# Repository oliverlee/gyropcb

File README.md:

This set of PCBs are designed to use with various projects in the
[phobos](https://github.com/oliverlee/phobos) repository. The PCBs are designed
to be used with the following items:
- [OLIMEX STM32-H405](https://www.olimex.com/Products/ARM/ST/STM32-H405/)
- [Maxon ESCON Module 50//5](http://www.maxonmotor.com/maxon/view/product/control/4-Q-Servokontroller/438725)

## Bill of Materials
The bill of materials is maintained [here](https://docs.google.com/spreadsheets/d/1CJe4dBAEXy64Y3e8YSP1X_Nll6x3aowWz7-QJbUk4VQ/edit?usp=sharing)

It may be out of date so take a look at it carefully.

## Notes
- In order to use the SDIO peripheral, R27 on the OLIMEX STM32-H405 must be
  disconnected from from the SDIO_CMD line (EXT1-11). This can be done by
  cutting the trace connecting EXT1-11 and R27.

## Errata
### v0.1
### mc pcb
- Description for solder jumper switch S3 on silkscreen layer is reversed.
- Description for solder jumper switch S4 on silkscreen layer is reversed.
- SDIO CMD line missing pullup resistor. A 33k resistor can be added at EXT1
  connecting pins 5 and 11. The leads must be kept as short as possible to
  minimize overshoot and ringing.

### power pcb
- +24V mount pad not connected to +24V rail.
- GND mount pad not connected to ground planes.
- The measure line of the Kistler torque sensor cannot be pulled to ground. A
  fix requires the removal of transistor Q2 and the measure line to be connected
  to the collector end of transistor Q1. This bypasses and disables switch S1.
- Description for solder jumper switch S2 on silkscreen layer is reversed.
- Silkscreen on J1, J3 incorrect: WIND1 and WIND2 reversed.
- Trace for HALL2_S2 between Ext3 and J3 is completely missing.
- J1, J3 molex pins can not withstand motor windings 1,2,3 current. Motor windings cable must be connected directly to motor dive. Check drawing for new molex types used to rearrange the new connection.
- J1, J2 male molex vertical headers must be changed with right hand angle headers to allow motor drive fit to Ext2 & Ext1. Check drawing file for new headers used to make the rearrangement.

For the steer by wire bicycle project the following changes were made:
### power pcb
18 Voltage regulator switched from LM2576S TO LM2576HV to withstand higher voltage since power supply voltage was switched from 24v to 36v.
### mc_pcb
Multiplexers 74AC157D were removed since Giel mentioned that there was an issue with the supply voltage. 
The inputs and outputs pins of the multiplexers were connected with cables. U4 now gives an output of ENC1_CHA+CHB and ENC2_CHA+CHB. 
Rear wheel encoder must be connected directly to microcontroller. U5 gives the output of PEDAL_ENC_A +ENC_B.

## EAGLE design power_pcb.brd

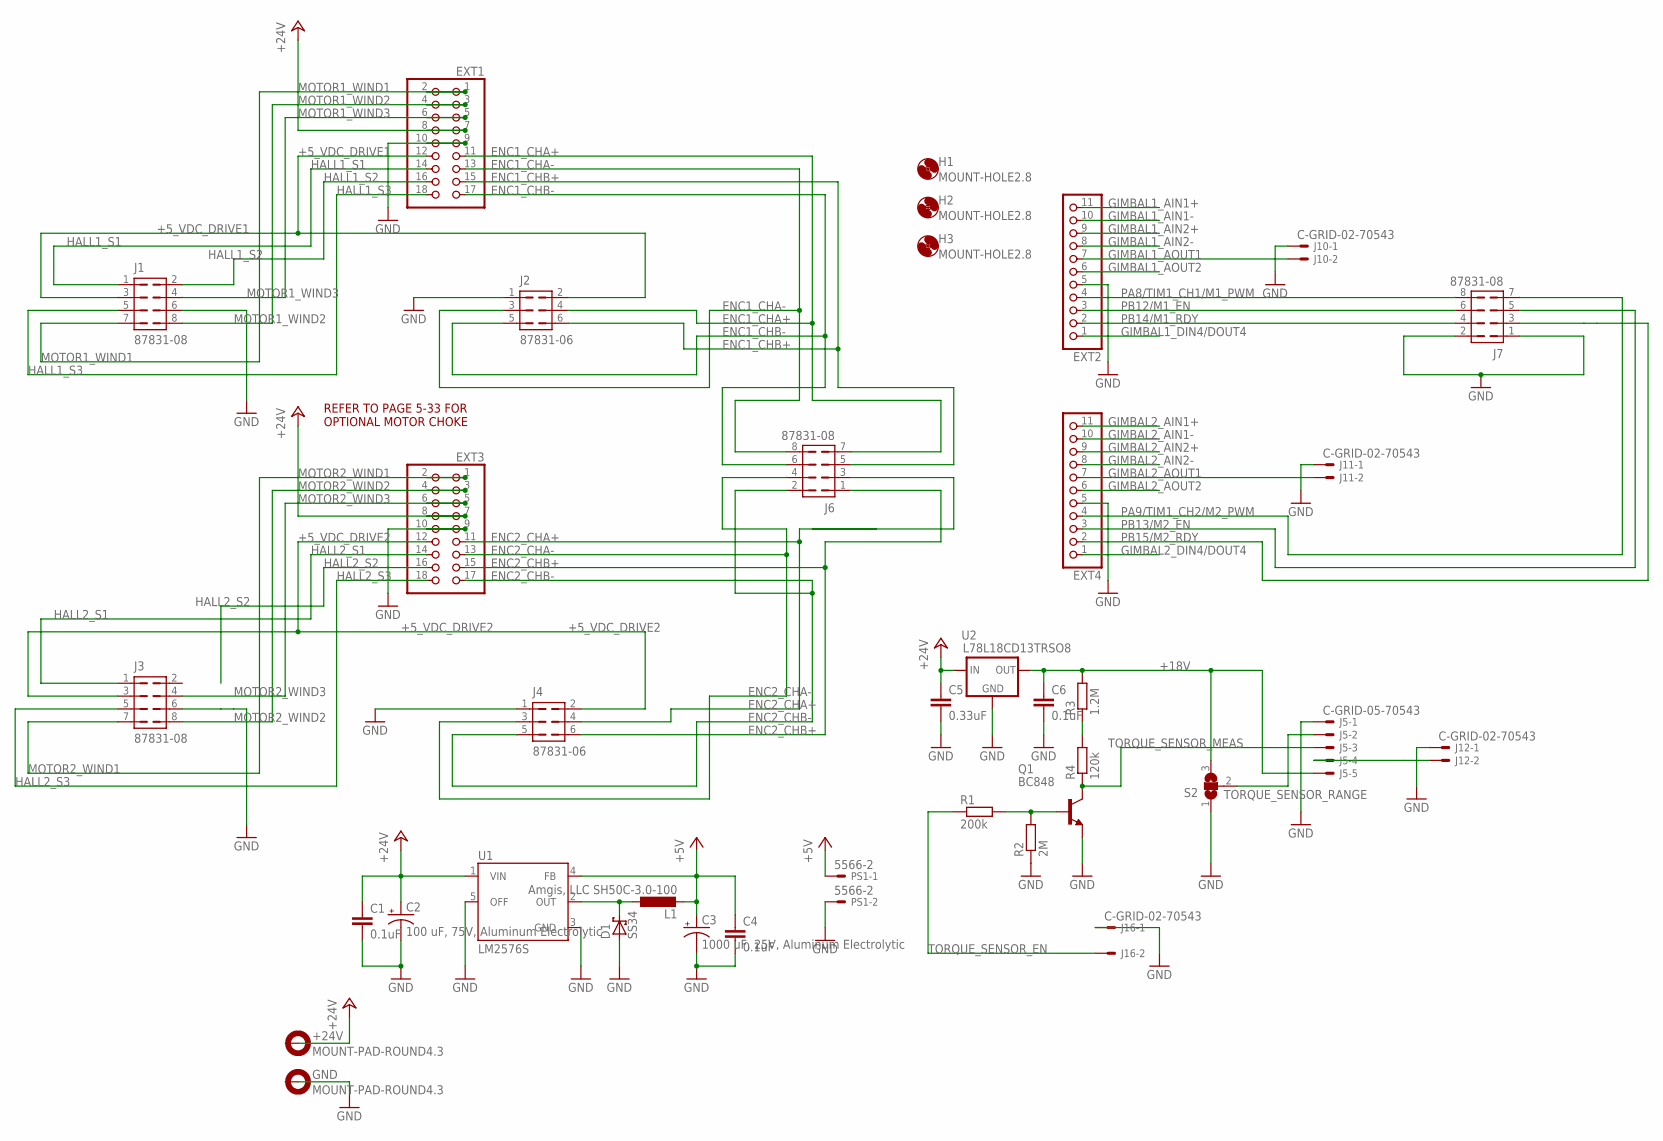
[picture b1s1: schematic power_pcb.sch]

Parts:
+24V: MOUNT-PAD-ROUND4.3; 4,3-PAD
C1, C4, C6: 0.1uF; C0603
C2: 100 uF, 75V, Aluminum Electrolytic; PANASONIC_H13
C3: 1000 uF, 25V, Aluminum Electrolytic; PANASONIC_H13
C5: 0.33uF; C0603
D1: SS34; SMC
EXT1, EXT3: PINHD-2X9; 2X09
EXT2, EXT4: PINHD-1X11; 1X11
GND: MOUNT-PAD-ROUND4.3; 4,3-PAD
H1, H2, H3: MOUNT-HOLE2.8; 2,8
J1, J3, J6, J7: 87831-08
J2, J4: 87831-06
J5: C-GRID-05-70543; 70543-05
J10, J11, J12, J16: C-GRID-02-70543; 70543-02
L1: Amgis, LLC SH50C-3.0-100; SH50C-C4
PS1: 5566-2
Q1: BC848; SOT23
R1: 200k; R0603
R2: 2M; R0603
R3: 1.2M; R1210
R4: 120k; R1210
S2: SJ2W; SJ_2
U1: LM2576S; TO263-5
U2: L78L18CD13TRSO8; SO8-VREG

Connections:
+5V: C3.+, C4.1, L1.P$2 (2), PS1.1, U1.4 (FB)
+5_VDC_DRIVE1: EXT1.12, J1.3, J2.2
+5_VDC_DRIVE2: EXT3.12, J3.3, J4.2
+18V: C6.1, J5.5, R3.2, S2.3, U2.1 (OUT)
+24V: C1.1, C2.+, C5.1, EXT1.7, EXT1.8, EXT3.7, EXT3.8, U1.1 (VIN), U2.8 (IN)
ENC1_CHA+: EXT1.11, J2.4, J6.7
ENC1_CHA-: EXT1.13, J2.3, J6.8
ENC1_CHB+: EXT1.15, J2.6, J6.5
ENC1_CHB-: EXT1.17, J2.5, J6.6
ENC2_CHA+: EXT3.11, J4.4, J6.3
ENC2_CHA-: EXT3.13, J4.3, J6.4
ENC2_CHB+: EXT3.15, J4.6, J6.1
ENC2_CHB-: EXT3.17, J4.5, J6.2
GIMBAL1_AIN1+: EXT2.11
GIMBAL1_AIN1-: EXT2.10
GIMBAL1_AIN2+: EXT2.9
GIMBAL1_AIN2-: EXT2.8
GIMBAL1_AOUT1: EXT2.7, J10.2
GIMBAL1_AOUT2: EXT2.6
GIMBAL1_DIN4/DOUT4: EXT2.1
GIMBAL2_AIN1+: EXT4.11
GIMBAL2_AIN1-: EXT4.10
GIMBAL2_AIN2+: EXT4.9
GIMBAL2_AIN2-: EXT4.8
GIMBAL2_AOUT1: EXT4.7, J11.2
GIMBAL2_AOUT2: EXT4.6
GIMBAL2_DIN4/DOUT4: EXT4.1
GND: C1.2, C2.-, C3.-, C4.2, C5.2, C6.2, D1.A, EXT1.9, EXT1.10, EXT2.5, EXT3.9, EXT3.10, EXT4.5, J1.6, J2.1, J3.6, J4.1, J5.1, J7.1, J7.2, J10.1, J11.1, J12.1, J16.1, PS1.2, Q1.2 (E), R2.1, S2.1, U1.3 (GND), U1.5 (OFF), U2.2 (GND), U2.3 (GND), U2.6 (GND), U2.7 (GND)
HALL1_S1: EXT1.14, J1.1
HALL1_S2: EXT1.16, J1.2
HALL1_S3: EXT1.18, J1.5
HALL2_S1: EXT3.14, J3.1
HALL2_S2: EXT3.16
HALL2_S3: EXT3.18, J3.5
MOTOR1_WIND1: EXT1.1, EXT1.2, J1.7
MOTOR1_WIND2: EXT1.3, EXT1.4, J1.8
MOTOR1_WIND3: EXT1.5, EXT1.6, J1.4
MOTOR2_WIND1: EXT3.1, EXT3.2, J3.7
MOTOR2_WIND2: EXT3.3, EXT3.4, J3.8
MOTOR2_WIND3: EXT3.5, EXT3.6, J3.4
unnamed: J5.4, J12.2
unnamed: D1.C, L1.P$1 (1), U1.2 (OUT)
unnamed: R3.1, R4.2
unnamed: Q1.1 (B), R1.2, R2.2
PA8/TIM1_CH1/M1_PWM: EXT2.4, J7.8
PA9/TIM1_CH2/M2_PWM: EXT4.4, J7.7
PB12/M1_EN: EXT2.3, J7.6
PB13/M2_EN: EXT4.3, J7.5
PB14/M1_RDY: EXT2.2, J7.4
PB15/M2_RDY: EXT4.2, J7.3
TORQUE_SENSOR_EN: J16.2, R1.1
TORQUE_SENSOR_MEAS: J5.3, Q1.3 (C), R4.1
TORQUE_SENSOR_RANGE: J5.2, S2.2

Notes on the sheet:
REFER TO PAGE 5-33 FOR OPTIONAL MOTOR CHOKE

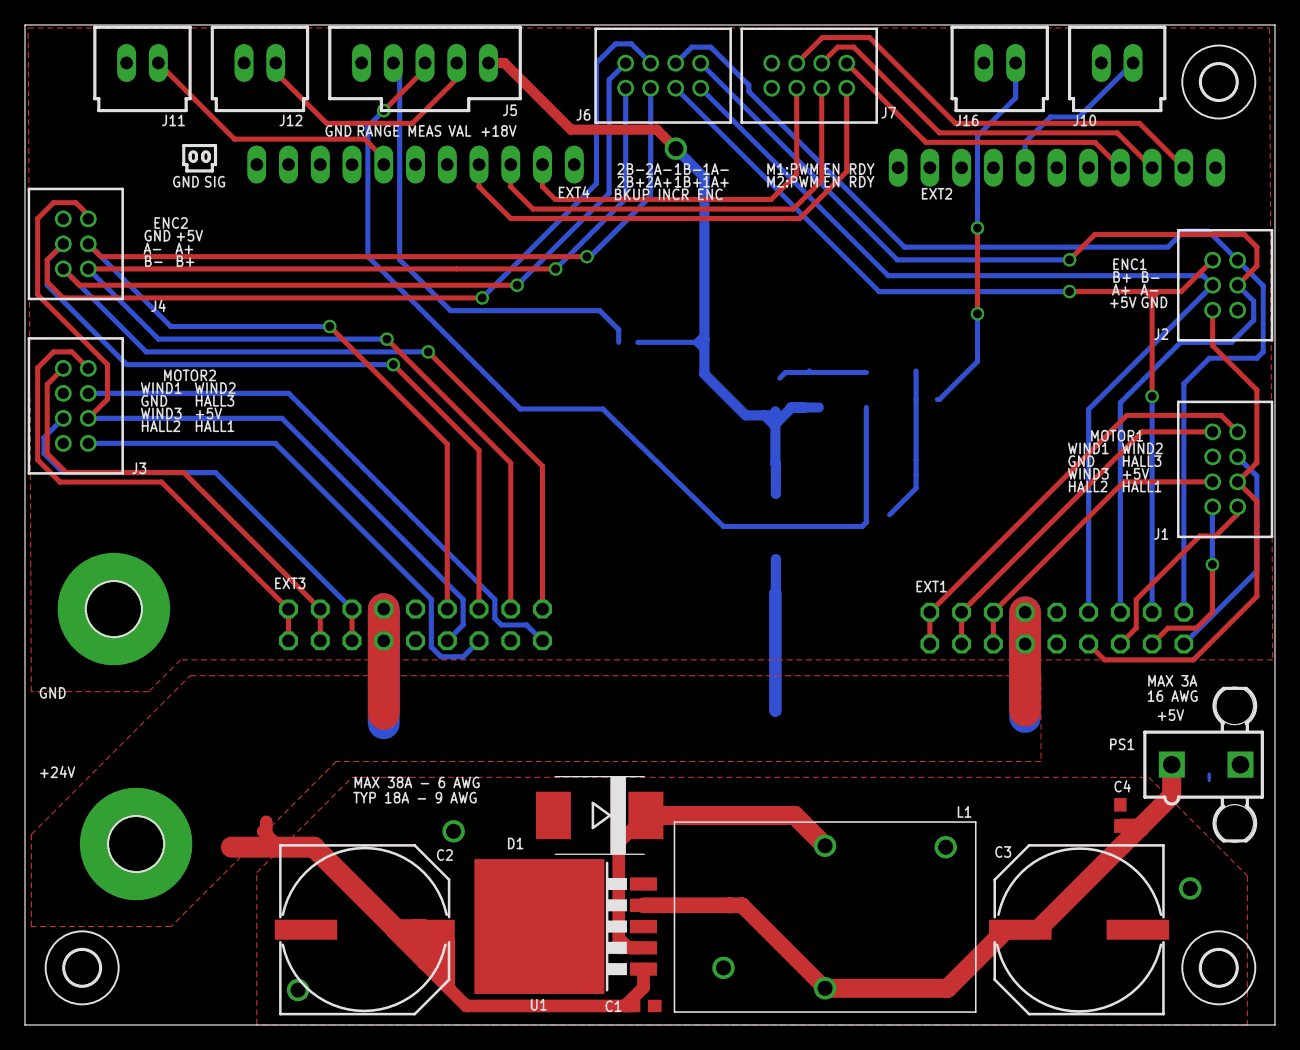
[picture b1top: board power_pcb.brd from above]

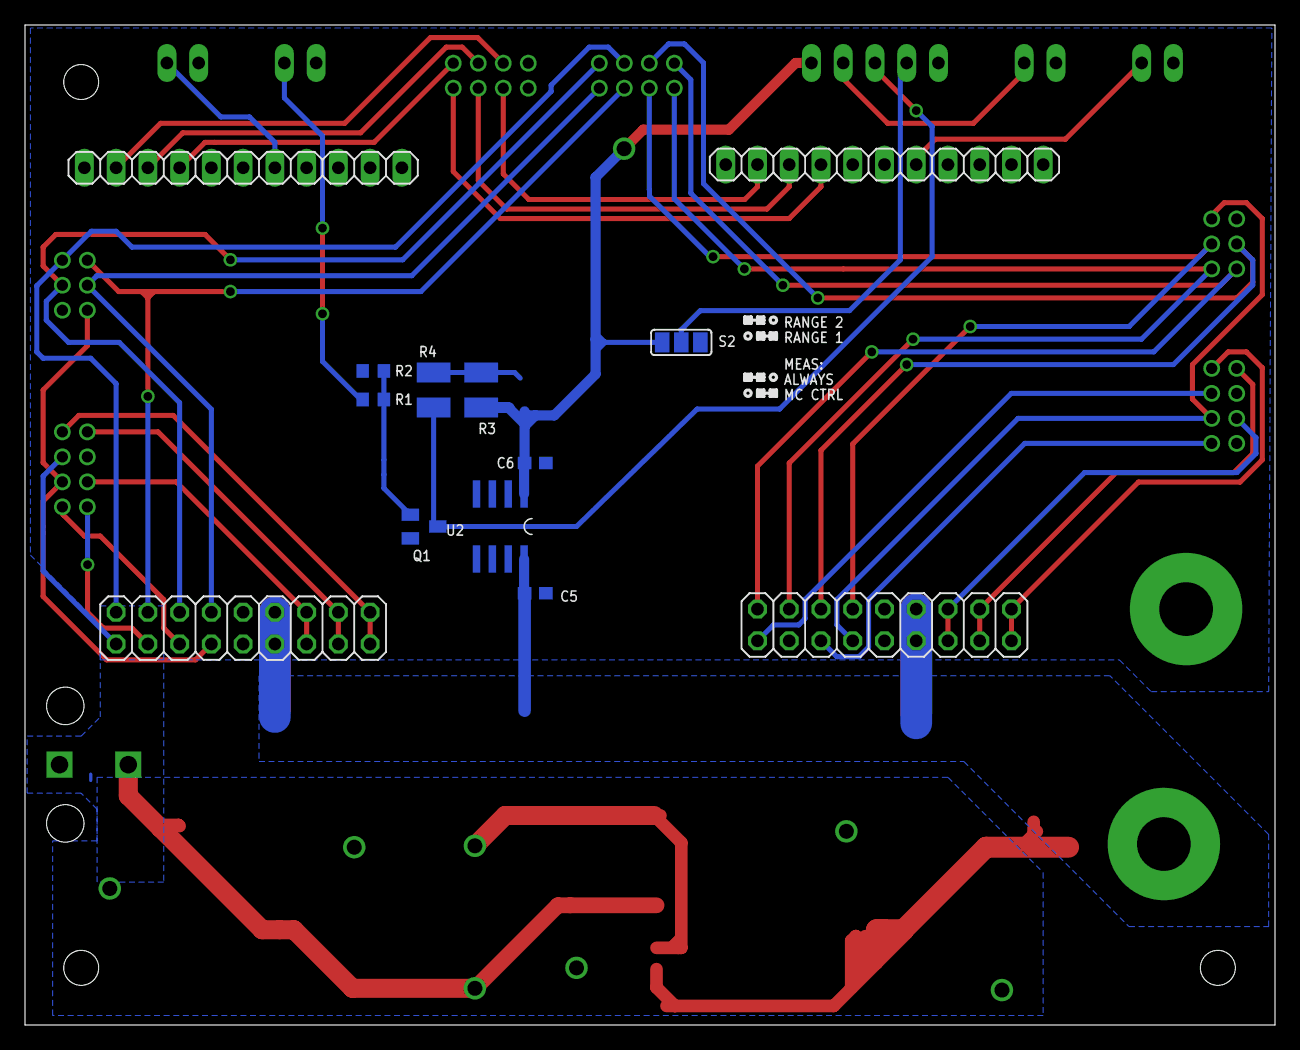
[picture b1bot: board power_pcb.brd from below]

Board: 8 copper layers, 100.0 x 80.0 mm, 37 parts (13 on the bottom side), 40 nets.

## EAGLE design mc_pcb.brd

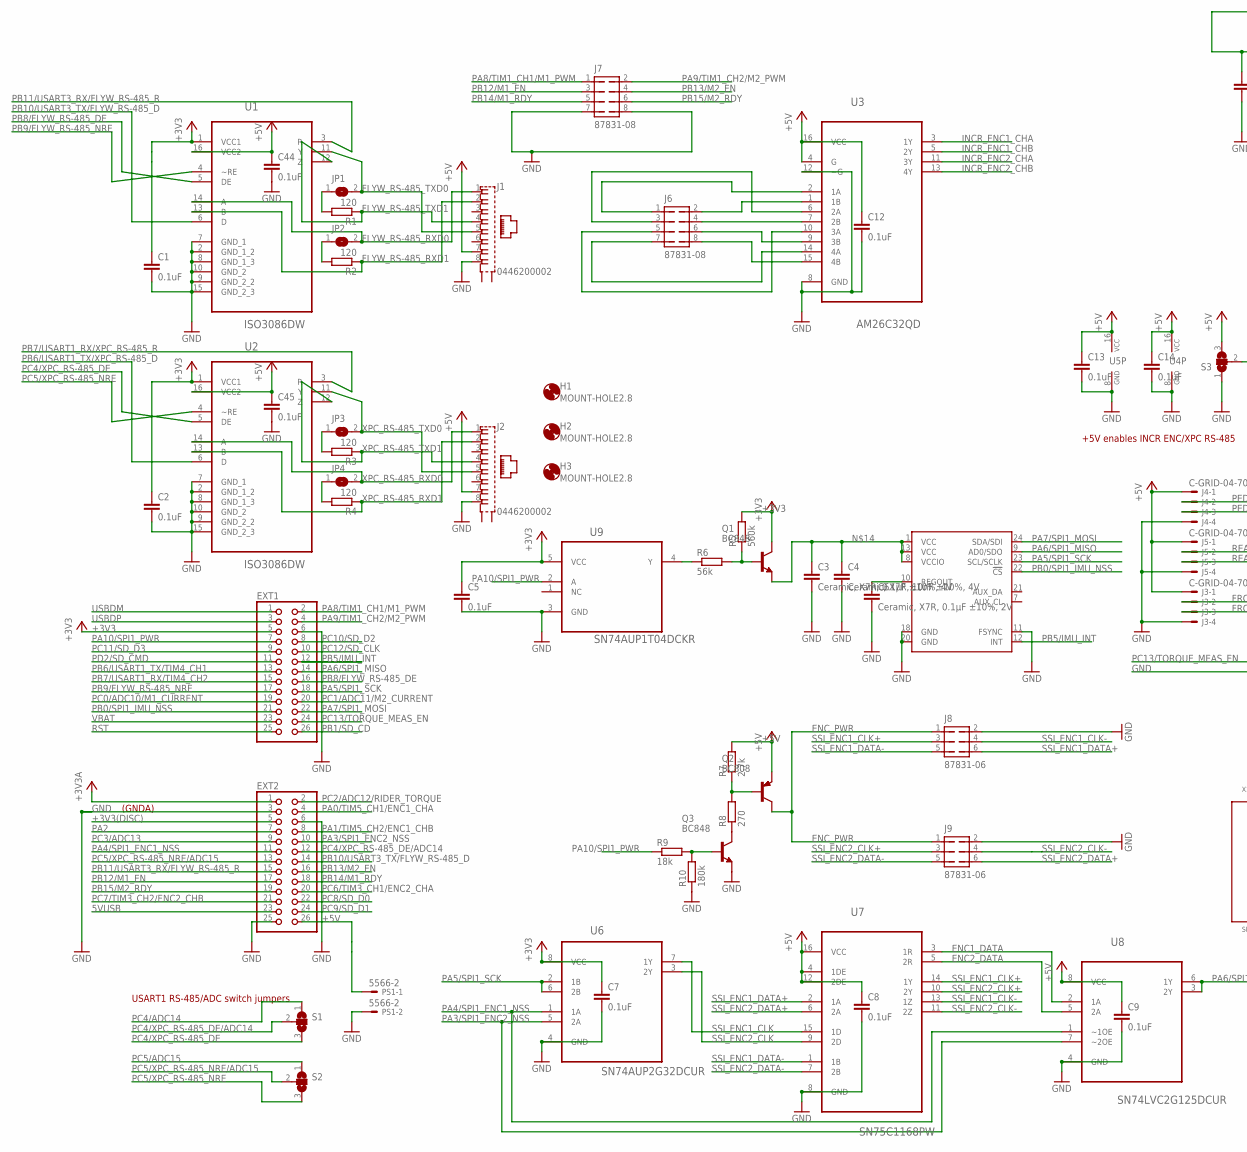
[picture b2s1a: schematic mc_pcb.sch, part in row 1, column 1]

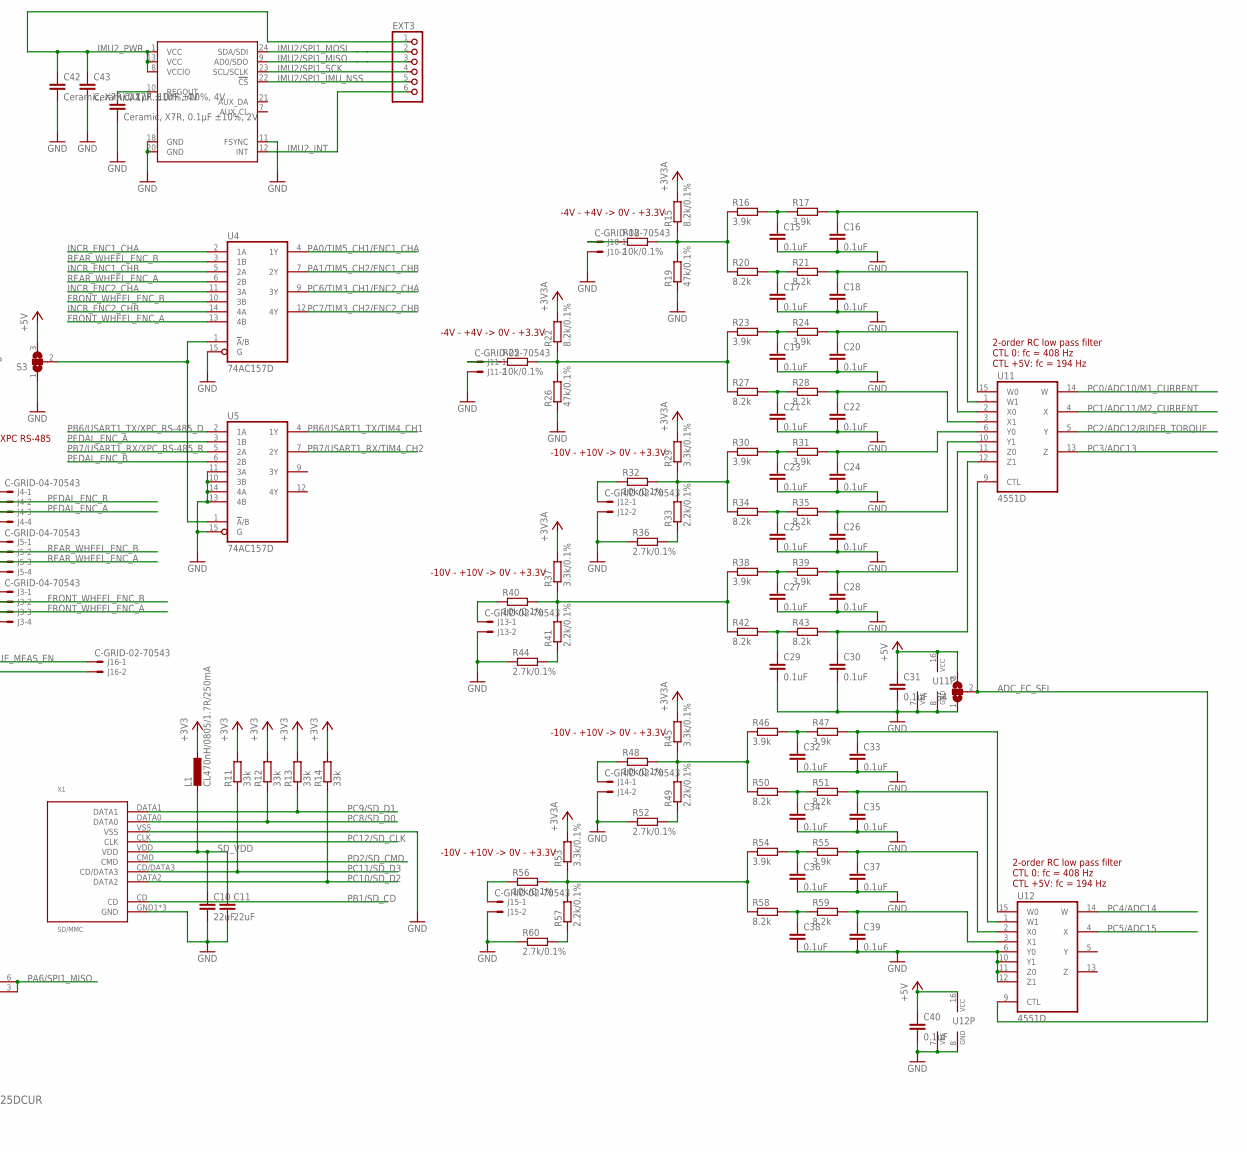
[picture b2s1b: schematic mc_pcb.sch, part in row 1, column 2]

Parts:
C1, C2, C5, C7, C8, C9, C12, C13, C14, C15, C16, C17, C18, C19, C20, C21, C22, C23, C24, C25, C26, C27, C28, C29, C30, C31, C32, C33, C34, C35, C36, C37, C38, C39, C40, C44, C45: 0.1uF; C0603
C3, C42: Ceramic, X7R, 0.1μF ±10%, 4V; C0603
C4, C43: Ceramic, X7R, 10nF ±10%, 4V; C0603
C6, C41: Ceramic, X7R, 0.1μF ±10%, 2V; C0603
C10, C11: 22uF; C0603
EXT1, EXT2: PINHD-2X13; 2X13
EXT3: PINHD-1X6; 1X06
H1, H2, H3: MOUNT-HOLE2.8; 2,8
J1, J2: 0446200002
J3, J4, J5: C-GRID-04-70543; 70543-04
J6, J7: 87831-08
J8, J9: 87831-06
J10, J11, J12, J13, J14, J15, J16: C-GRID-02-70543; 70543-02
JP1, JP2, JP3, JP4: SJ
L1: CL470nH/0805/1.7R/250mA; L2012C
PS1: 5566-2
Q1, Q3: BC848; SOT23
Q2: BC808; SOT23-BEC
R1, R2, R3, R4: 120; R0603
R5: 560k; R0603
R6: 56k; R0603
R7: 2.7k; R1210
R8: 270; R1210
R9: 18k; R0603
R10: 180k; R0603
R11, R12, R13, R14: 33k; R0603
R15, R22: 8.2k/0.1%; R0603
R16, R17, R23, R24, R30, R31, R38, R39, R46, R47, R54, R55: 3.9k; R0603
R18, R25, R32, R40, R48, R56: 10k/0.1%; R0603
R19, R26: 47k/0.1%; R0603
R20, R21, R27, R28, R34, R35, R42, R43, R50, R51, R58, R59: 8.2k; R0603
R29, R37, R45, R53: 3.3k/0.1%; R0603
R33, R41, R49, R57: 2.2k/0.1%; R0603
R36, R44, R52, R60: 2.7k/0.1%; R0603
S1, S2, S3, S4: SJ2W; SJ_2
U1, U2: ISO3086DW; SOIC127P1030X265-16N
U3: AM26C32QD; SOIC127P600X175-16N
U4, U5: 74AC157D; SO16
U6: SN74AUP2G32DCUR; SOP50P310X90-8N
U7: SN75C1168PW; SOP65P640X120-16N
U8: SN74LVC2G125DCUR; SOP50P310X90-8N
U9: SN74AUP1T04DCKR; SOT65P210X110-5N
U10, U13: MPU-9250; QFN24-SMALL
U11, U12: 4551D; SO16
X1: 10100660; -68-6

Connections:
5VUSB: EXT2.23
+3V3: C1.1, C2.1, C5.1, C7.1, EXT1.5, L1.1, Q1.3 (C), R5.2, R11.2, R12.2, R13.2, R14.2, U1.1 (VCC1), U2.1 (VCC1), U6.8 (VCC), U9.5 (VCC)
+3V3(DISC): EXT2.5
+3V3A: EXT2.1, R15.2, R22.2, R29.2, R37.2, R45.2, R53.2
+5V: C8.1, C9.1, C12.1, C13.1, C14.1, C31.1, C40.1, C44.1, C45.1, EXT2.26, J1.7, J2.7, J3.1, J4.1, J5.1, PS1.1, Q2.E, R7.2, S3.3, S4.3, U1.16 (VCC2), U2.16 (VCC2), U3.4 (G), U3.16 (VCC), U4.16 (VCC), U5.16 (VCC), U7.4 (1DE), U7.12 (2DE), U7.16 (VCC), U8.8 (VCC), U11.16 (VCC), U12.16 (VCC)
ADC_FC_SEL: S4.2, U11.9 (CTL), U12.9 (CTL)
ENC1_CHA+: J6.2, U3.1 (1B)
ENC1_CHA-: J6.1, U3.2 (1A)
ENC1_CHB+: J6.4, U3.7 (2B)
ENC1_CHB-: J6.3, U3.6 (2A)
ENC1_DATA: U7.3 (1R), U8.2 (1A)
ENC2_CHA+: J6.6, U3.9 (3B)
ENC2_CHA-: J6.5, U3.10 (3A)
ENC2_CHB+: J6.8, U3.15 (4B)
ENC2_CHB-: J6.7, U3.14 (4A)
ENC2_DATA: U7.5 (2R), U8.5 (2A)
ENC_PWR: J8.1, J9.1, Q2.C
FLYW_RS-485_RXD0: J1.1, JP2.2, U1.14 (A)
FLYW_RS-485_RXD1: J1.2, R2.1, U1.13 (B)
FLYW_RS-485_TXD0: J1.5, JP1.2, U1.11 (Y)
FLYW_RS-485_TXD1: J1.4, R1.1, U1.12 (Z)
FRONT_WHEEL_ENC_A: J3.3, U4.13 (4B)
FRONT_WHEEL_ENC_B: J3.2, U4.10 (3B)
GND: C1.2, C2.2, C3.2, C4.2, C5.2, C6.2, C7.2, C8.2, C9.2, C10.2, C11.2, C12.2, C13.2, C14.2, C15.2, C16.2, C17.2, C18.2, C19.2, C20.2, C21.2, C22.2, C23.2, C24.2, C25.2, C26.2, C27.2, C28.2, C29.2, C30.2, C31.2, C32.2, C33.2, C34.2, C35.2, C36.2, C37.2, C38.2, C39.2, C40.2, C41.2, C42.2, C43.2, C44.2, C45.2, EXT1.6, EXT2.3, EXT2.6, EXT2.25, J1.8, J2.8, J3.4, J4.4, J5.4, J7.7, J7.8, J8.2, J9.2, J10.2, J11.2, J12.2, J13.2, J14.2, J15.2, J16.2, PS1.2, Q3.2 (E), R10.1, R19.1, R26.1, R36.1, R44.1, R52.1, R60.1, S3.1, S4.1, U1.2 (GND_1_2), U1.7 (GND_1), U1.8 (GND_1_3), U1.9 (GND_2_2), U1.10 (GND_2), U1.15 (GND_2_3), U2.2 (GND_1_2), U2.7 (GND_1), U2.8 (GND_1_3), U2.9 (GND_2_2), U2.10 (GND_2), U2.15 (GND_2_3), U3.8 (GND), U3.12 (~G), U4.8 (GND), U4.15 (G), U5.8 (GND), U5.10 (3B), U5.11 (3A), U5.13 (4B), U5.14 (4A), U5.15 (G), U6.4 (GND), U7.8 (GND), U8.4 (GND), U9.3 (GND), U10.11 (FSYNC), U10.18 (GND), U10.20 (GND), U11.7 (VEE), U11.8 (GND), U12.6 (Y0), U12.7 (VEE), U12.8 (GND), U12.10 (Y1), U12.11 (Z0), U12.12 (Z1), U13.11 (FSYNC), U13.18 (GND), U13.20 (GND), X1.GND1 (GND), X1.GND2 (GND), X1.GND3 (GND), X1.VSS
IMU2/SPI1_IMU_NSS: EXT3.5, U13.22 (!CS)
IMU2/SPI1_MISO: EXT3.3, U13.9 (AD0/SDO)
IMU2/SPI1_MOSI: EXT3.2, U13.24 (SDA/SDI)
IMU2/SPI1_SCK: EXT3.4, U13.23 (SCL/SCLK)
IMU2_INT: EXT3.6, U13.12 (INT)
IMU2_PWR: C42.1, C43.1, EXT3.1, U13.1 (VCC), U13.8 (VCCIO), U13.13 (VCC)
INCR_ENC1_CHA: U3.3 (1Y), U4.2 (1A)
INCR_ENC1_CHB: U3.5 (2Y), U4.5 (2A)
INCR_ENC2_CHA: U3.11 (3Y), U4.11 (3A)
INCR_ENC2_CHB: U3.13 (4Y), U4.14 (4A)
unnamed: C6.1, U10.10 (REGOUT)
unnamed: Q1.1 (B), R5.1, R6.2
unnamed: Q2.B, R7.1, R8.2
unnamed: Q3.3 (C), R8.1
unnamed: Q3.1 (B), R9.2, R10.2
unnamed: R33.1, R36.2
unnamed: R29.1, R30.1, R32.2, R33.2, R34.1
unnamed: C41.1, U13.10 (REGOUT)
unnamed: C3.1, C4.1, Q1.2 (E), U10.1 (VCC), U10.8 (VCCIO), U10.13 (VCC)
unnamed: R15.1, R16.1, R18.2, R19.2, R20.1
unnamed: R37.1, R38.1, R40.2, R41.2, R42.1
unnamed: JP1.1, R1.2
unnamed: JP3.1, R3.2
unnamed: C32.1, R46.2, R47.1
unnamed: C33.1, R47.2, U12.15 (W0)
unnamed: C34.1, R50.2, R51.1
unnamed: C35.1, R51.2, U12.1 (W1)
unnamed: C36.1, R54.2, R55.1
unnamed: C37.1, R55.2, U12.2 (X0)
unnamed: C38.1, R58.2, R59.1
unnamed: C39.1, R59.2, U12.3 (X1)
unnamed: R6.1, U9.4 (Y)
unnamed: J15.1, R56.1
unnamed: R22.1, R23.1, R25.2, R26.2, R27.1
unnamed: J14.1, R48.1
unnamed: S3.2, U4.1 (!A!/B), U5.1 (!A!/B)
unnamed: J12.1, R32.1
unnamed: JP2.1, R2.2
unnamed: JP4.1, R4.2
unnamed: J10.1, R18.1
unnamed: C23.1, R30.2, R31.1
unnamed: C24.1, R31.2, U11.6 (Y0)
unnamed: R41.1, R44.2
unnamed: R45.1, R46.1, R48.2, R49.2, R50.1
unnamed: R49.1, R52.2
unnamed: R53.1, R54.1, R56.2, R57.2, R58.1
unnamed: R57.1, R60.2
unnamed: J13.1, R40.1
unnamed: C25.1, R34.2, R35.1
unnamed: C26.1, R35.2, U11.10 (Y1)
unnamed: C27.1, R38.2, R39.1
unnamed: C28.1, R39.2, U11.11 (Z0)
unnamed: C29.1, R42.2, R43.1
unnamed: C30.1, R43.2, U11.12 (Z1)
unnamed: C15.1, R16.2, R17.1
unnamed: C16.1, R17.2, U11.15 (W0)
unnamed: C17.1, R20.2, R21.1
unnamed: C18.1, R21.2, U11.1 (W1)
unnamed: C19.1, R23.2, R24.1
unnamed: C20.1, R24.2, U11.2 (X0)
unnamed: C21.1, R27.2, R28.1
unnamed: C22.1, R28.2, U11.3 (X1)
PA0/TIM5_CH1/ENC1_CHA: EXT2.4, U4.4 (1Y)
PA1/TIM5_CH2/ENC1_CHB: EXT2.8, U4.7 (2Y)
PA2: EXT2.7
PA3/SPI1_ENC2_NSS: EXT2.10, U6.5 (2A), U8.7 (~2OE)
PA4/SPI1_ENC1_NSS: EXT2.11, U6.1 (1A), U8.1 (~1OE)
PA5/SPI1_SCK: EXT1.18, U6.2 (1B), U6.6 (2B), U10.23 (SCL/SCLK)
PA6/SPI1_MISO: EXT1.14, U8.3 (2Y), U8.6 (1Y), U10.9 (AD0/SDO)
PA7/SPI1_MOSI: EXT1.22, U10.24 (SDA/SDI)
PA8/TIM1_CH1/M1_PWM: EXT1.2, J7.1
PA9/TIM1_CH2/M2_PWM: EXT1.4, J7.2
PA10/SPI1_PWR: EXT1.7, R9.1, U9.2 (A)
PB0/SPI1_IMU_NSS: EXT1.21, U10.22 (!CS)
PB1/SD_CD: EXT1.26, X1.CD
PB5/IMU_INT: EXT1.12, U10.12 (INT)
PB6/USART1_TX/TIM4_CH1: EXT1.13, U5.4 (1Y)
PB6/USART1_TX/XPC_RS-485_D: U2.6 (D), U5.2 (1A)
PB7/USART1_RX/TIM4_CH2: EXT1.15, U5.7 (2Y)
PB7/USART1_RX/XPC_RS-485_R: U2.3 (R), U5.5 (2A)
PB8/FLYW_RS-485_DE: EXT1.16, U1.5 (DE)
PB9/FLYW_RS-485_NRE: EXT1.17, U1.4 (~RE)
PB10/USART3_TX/FLYW_RS-485_D: EXT2.14, U1.6 (D)
PB11/USART3_RX/FLYW_RS-485_R: EXT2.15, U1.3 (R)
PB12/M1_EN: EXT2.17, J7.3
PB13/M2_EN: EXT2.16, J7.4
PB14/M1_RDY: EXT2.18, J7.5
PB15/M2_RDY: EXT2.19, J7.6
PC0/ADC10/M1_CURRENT: EXT1.19, U11.14 (W)
PC1/ADC11/M2_CURRENT: EXT1.20, U11.4 (X)
PC2/ADC12/RIDER_TORQUE: EXT2.2, U11.5 (Y)
PC3/ADC13: EXT2.9, U11.13 (Z)
PC4/ADC14: S1.1, U12.14 (W)
PC4/XPC_RS-485_DE: S1.3, U2.5 (DE)
PC4/XPC_RS-485_DE/ADC14: EXT2.12, S1.2
PC5/ADC15: S2.1, U12.4 (X)
PC5/XPC_RS-485_NRE: S2.3, U2.4 (~RE)
PC5/XPC_RS-485_NRE/ADC15: EXT2.13, S2.2
PC6/TIM3_CH1/ENC2_CHA: EXT2.20, U4.9 (3Y)
PC7/TIM3_CH2/ENC2_CHB: EXT2.21, U4.12 (4Y)
PC8/SD_D0: EXT2.22, R12.1, X1.DATA0
PC9/SD_D1: EXT2.24, R13.1, X1.DATA1
PC10/SD_D2: EXT1.8, R14.1, X1.DATA2
PC11/SD_D3: EXT1.9, R11.1, X1.CD/DATA3
PC12/SD_CLK: EXT1.10, X1.CLK
PC13/TORQUE_MEAS_EN: EXT1.24, J16.1
PD2/SD_CMD: EXT1.11, X1.CMD
PEDAL_ENC_A: J4.3, U5.3 (1B)
PEDAL_ENC_B: J4.2, U5.6 (2B)
REAR_WHEEL_ENC_A: J5.3, U4.6 (2B)
REAR_WHEEL_ENC_B: J5.2, U4.3 (1B)
RST: EXT1.25
SD_VDD: C10.1, C11.1, L1.2, X1.VDD
SSI_ENC1_CLK: U6.7 (1Y), U7.15 (1D)
SSI_ENC1_CLK+: J8.3, U7.14 (1Y)
SSI_ENC1_CLK-: J8.4, U7.13 (1Z)
SSI_ENC1_DATA+: J8.6, U7.2 (1A)
SSI_ENC1_DATA-: J8.5, U7.1 (1B)
SSI_ENC2_CLK: U6.3 (2Y), U7.9 (2D)
SSI_ENC2_CLK+: J9.3, U7.10 (2Y)
SSI_ENC2_CLK-: J9.4, U7.11 (2Z)
SSI_ENC2_DATA+: J9.6, U7.6 (2A)
SSI_ENC2_DATA-: J9.5, U7.7 (2B)
USBDM: EXT1.1
USBDP: EXT1.3
VBAT: EXT1.23
X124: J11.1, R25.1
XPC_RS-485_RXD0: J2.1, JP4.2, U2.14 (A)
XPC_RS-485_RXD1: J2.2, R4.1, U2.13 (B)
XPC_RS-485_TXD0: J2.5, JP3.2, U2.11 (Y)
XPC_RS-485_TXD1: J2.4, R3.1, U2.12 (Z)

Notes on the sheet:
-4V - +4V -> 0V - +3.3V
2-order RC low pass filter CTL 0: fc = 408 Hz CTL +5V: fc = 194 Hz
-10V - +10V -> 0V - +3.3V
+5V enables INCR ENC/XPC RS-485
USART1 RS-485/ADC switch jumpers
(GNDA)

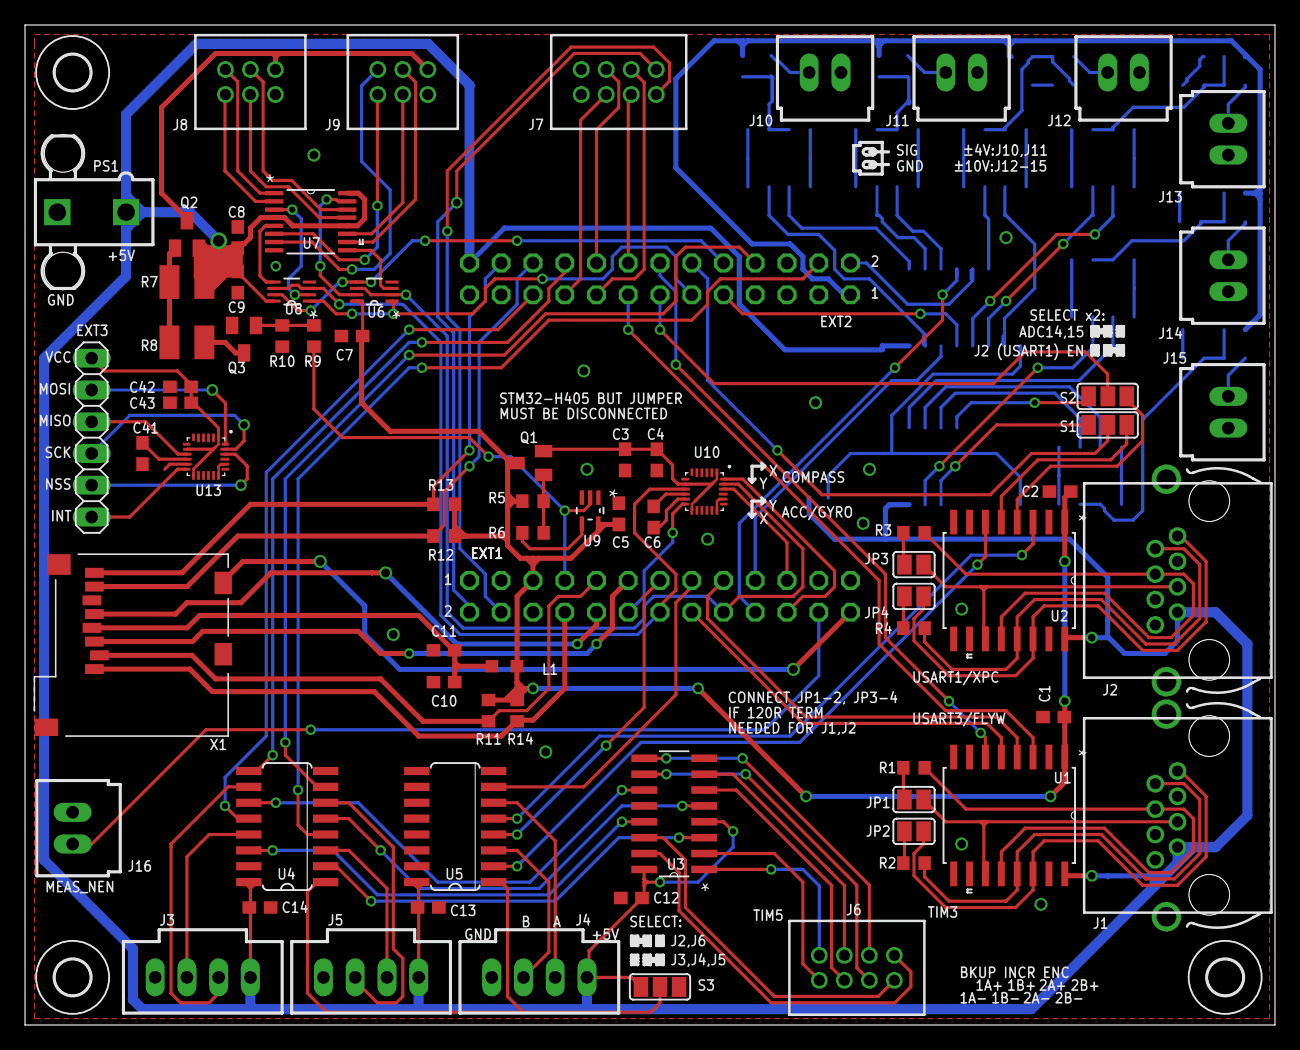
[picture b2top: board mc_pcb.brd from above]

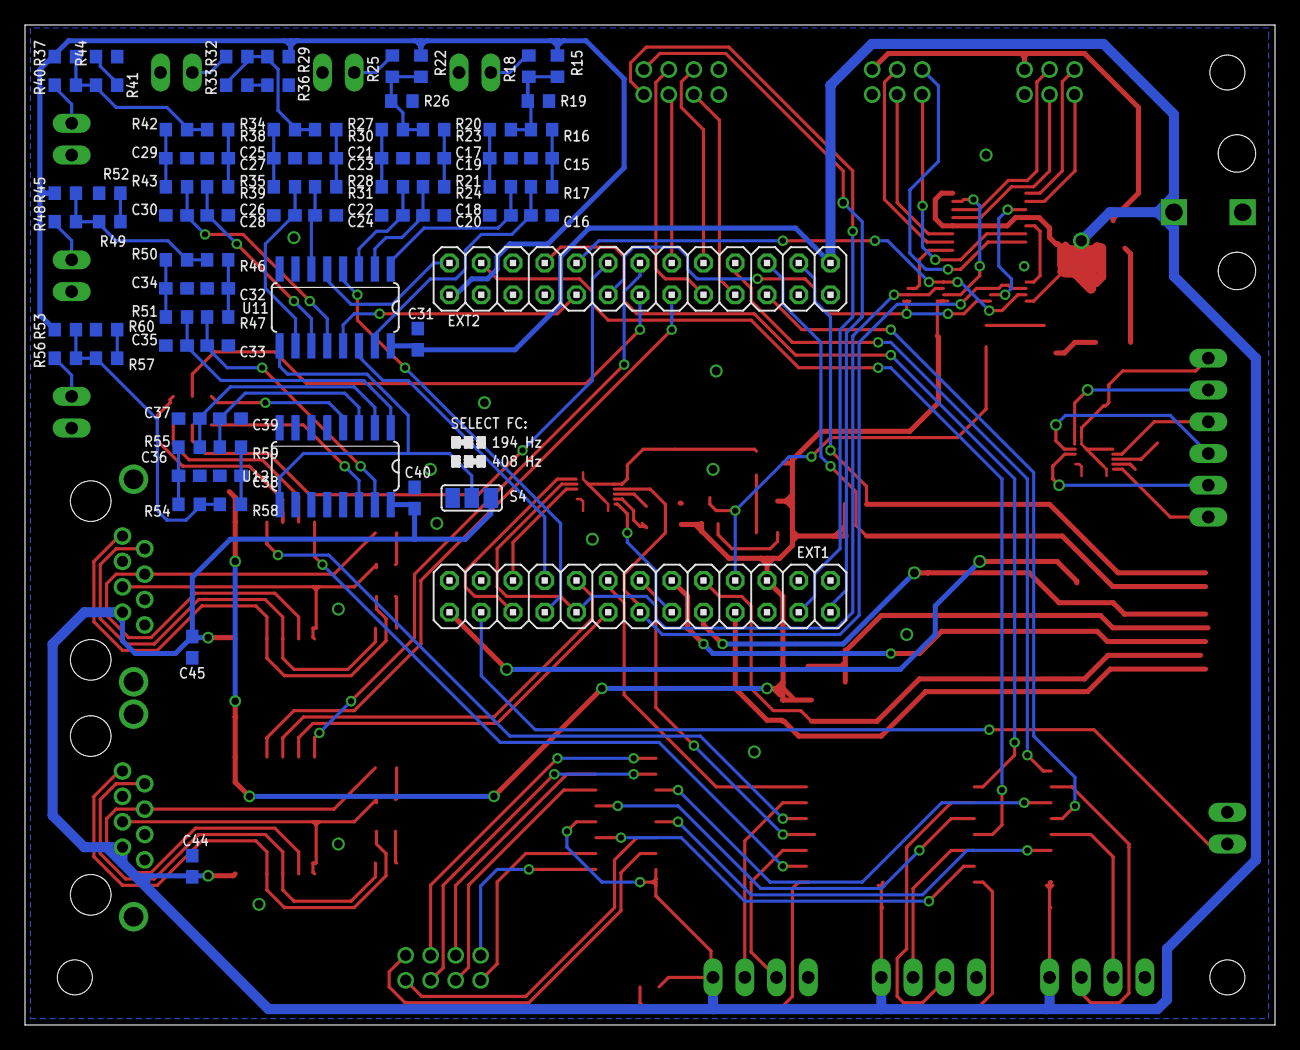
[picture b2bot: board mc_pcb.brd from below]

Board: 2 copper layers, 100.0 x 80.0 mm, 154 parts (79 on the bottom side), 148 nets.

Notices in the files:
parts and their libraries:
SparkFun-Capacitors: Licensing: Creative Commons ShareAlike 4.0 International - https://creativecommons.org/licenses/by-sa/4.0
